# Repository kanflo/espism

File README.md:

# Espism

This repo contins schematics and code to build a low cost ISM radio to wifi gateway.

Look at [hardware/v4](https://github.com/kanflo/espism/tree/master/hardware/v4) for the hardware and [verification](https://github.com/kanflo/espism/tree/master/verification) for the software used to do hardware verification. The directory [mqtt_sniffer](https://github.com/kanflo/espism/tree/master/mqtt_sniffer) contains an ISM to MQTT sniffer. Blog post [is here](http://johan.kanflo.com/bridging-ism-radio-and-wifi-for-lunch-money/).

#### Building

```
git clone https://github.com/kanflo/espism.git
cd espism
git submodule init && git submodule update
cd mqtt_sniffer
vi esp-open-rtos/include/private_ssid_config.h # Fix wifi credentials
make && make flash
```

Wifi credentials, in case you did not know, are written to `esp-open-rtos/include/private_ssid_config.h` as 

```
#define WIFI_SSID "your ssid"
#define WIFI_PASS "your key"
```

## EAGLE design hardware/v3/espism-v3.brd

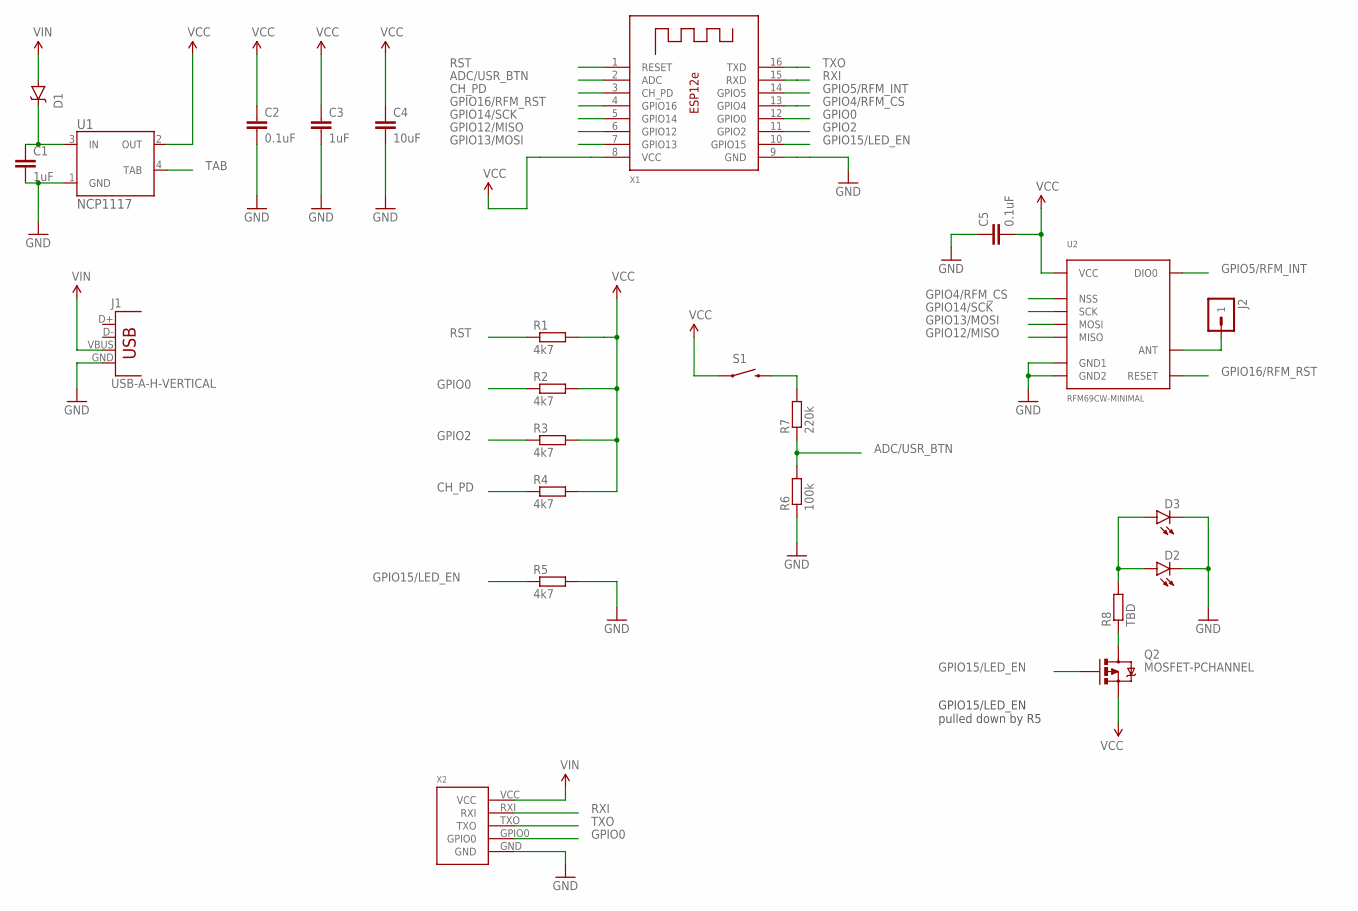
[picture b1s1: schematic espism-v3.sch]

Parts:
C1, C3: 1uF; 0603-CAP
C2, C5: 0.1uF; 0603-CAP
C4: 10uF; 0603-CAP
D1: DIODE-SCHOTTKYSOD-123FL; SOD-123FL
D2, D3: LED0603; LED-0603
J1: USB-A-H-VERTICAL
J2: M01-ANTENNA; 1X01-ANTENNA
Q2: MOSFET-PCHANNEL; SOT23-3
R1, R2, R3, R4, R5: 4k7; R0603
R6: 100k; R0603
R7: 220k; R0603
R8: TBD; R0603
S1: SWITCH-MOMENTARY-2SMD-1101NE; TACTILE-SWITCH-1101NE
U1: NCP1117; SOT223
U2: RFM69CW-MINIMAL
X1: ESP-12E
X2: ESPROGESPROG-DEVICE; ESPROG

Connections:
ADC/USR_BTN: R6.2, R7.1, X1.2 (ADC)
CAM_VCC: Q2.3 (D), R8.1
CH_PD: R4.1, X1.3 (CH_PD)
GND: C1.2, C2.2, C3.2, C4.2, C5.1, D2.C, D3.C, J1.GND, R5.2, R6.1, U1.1 (GND), U2.GND@1 (GND1), U2.GND@2 (GND2), X1.9 (GND), X2.GND
GPIO0: R2.1, X1.12 (GPIO0), X2.GPIO0
GPIO2: R3.1, X1.11 (GPIO2)
GPIO4/RFM_CS: U2.NSS, X1.13 (GPIO4)
GPIO5/RFM_INT: U2.DIO0, X1.14 (GPIO5)
GPIO12/MISO: U2.MISO, X1.6 (GPIO12)
GPIO13/MOSI: U2.MOSI, X1.7 (GPIO13)
GPIO14/SCK: U2.SCK, X1.5 (GPIO14)
GPIO15/LED_EN: Q2.1 (G), R5.1, X1.10 (GPIO15)
GPIO16/RFM_RST: U2.RESET, X1.4 (GPIO16)
unnamed: D2.A, D3.A, R8.2
unnamed: C1.1, D1.C, U1.3 (IN)
unnamed: J2.1, U2.ANT
unnamed: R7.2, S1.2
RST: R1.1, X1.1 (RESET)
RXI: X1.15 (RXD), X2.RXI
TAB: U1.4 (TAB)
TXO: X1.16 (TXD), X2.TXO
VCC: C2.1, C3.1, C4.1, C5.2, Q2.2 (S), R1.2, R2.2, R3.2, R4.2, S1.1, U1.2 (OUT), U2.VDD (VCC), X1.8 (VCC)
VIN: D1.A, J1.VBUS, X2.VCC

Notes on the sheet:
GPIO15/LED_EN pulled down by R5

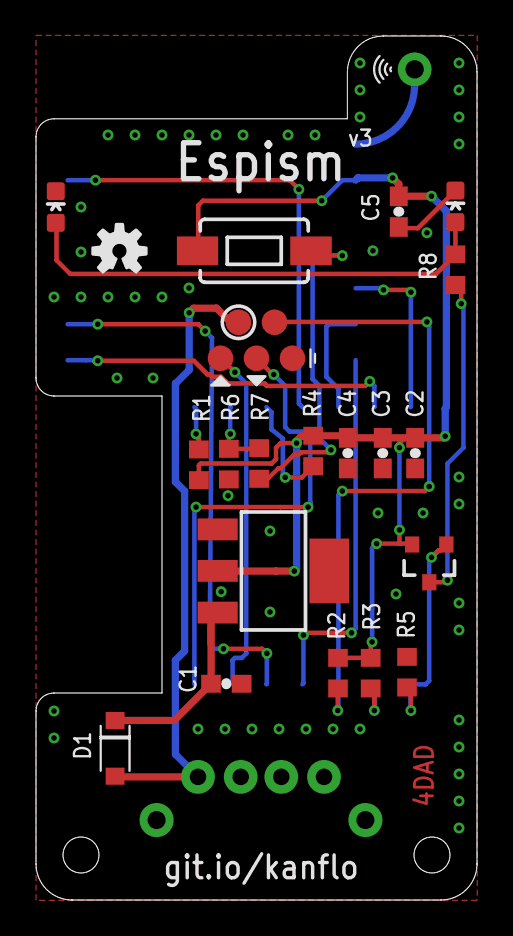
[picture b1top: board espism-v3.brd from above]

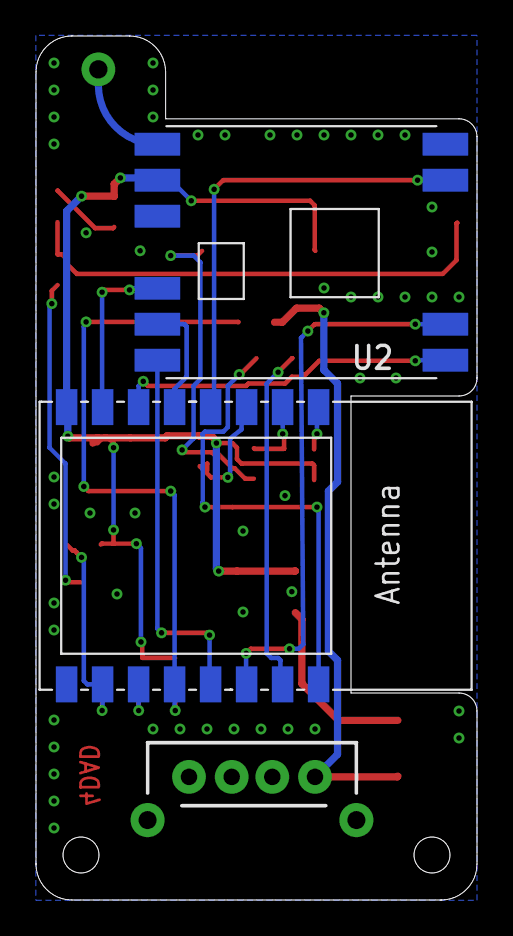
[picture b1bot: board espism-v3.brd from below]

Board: 2 copper layers, 24.5 x 48.0 mm, 25 parts (3 on the bottom side), 22 nets.

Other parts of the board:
U$2: OSHW-LOGO-S

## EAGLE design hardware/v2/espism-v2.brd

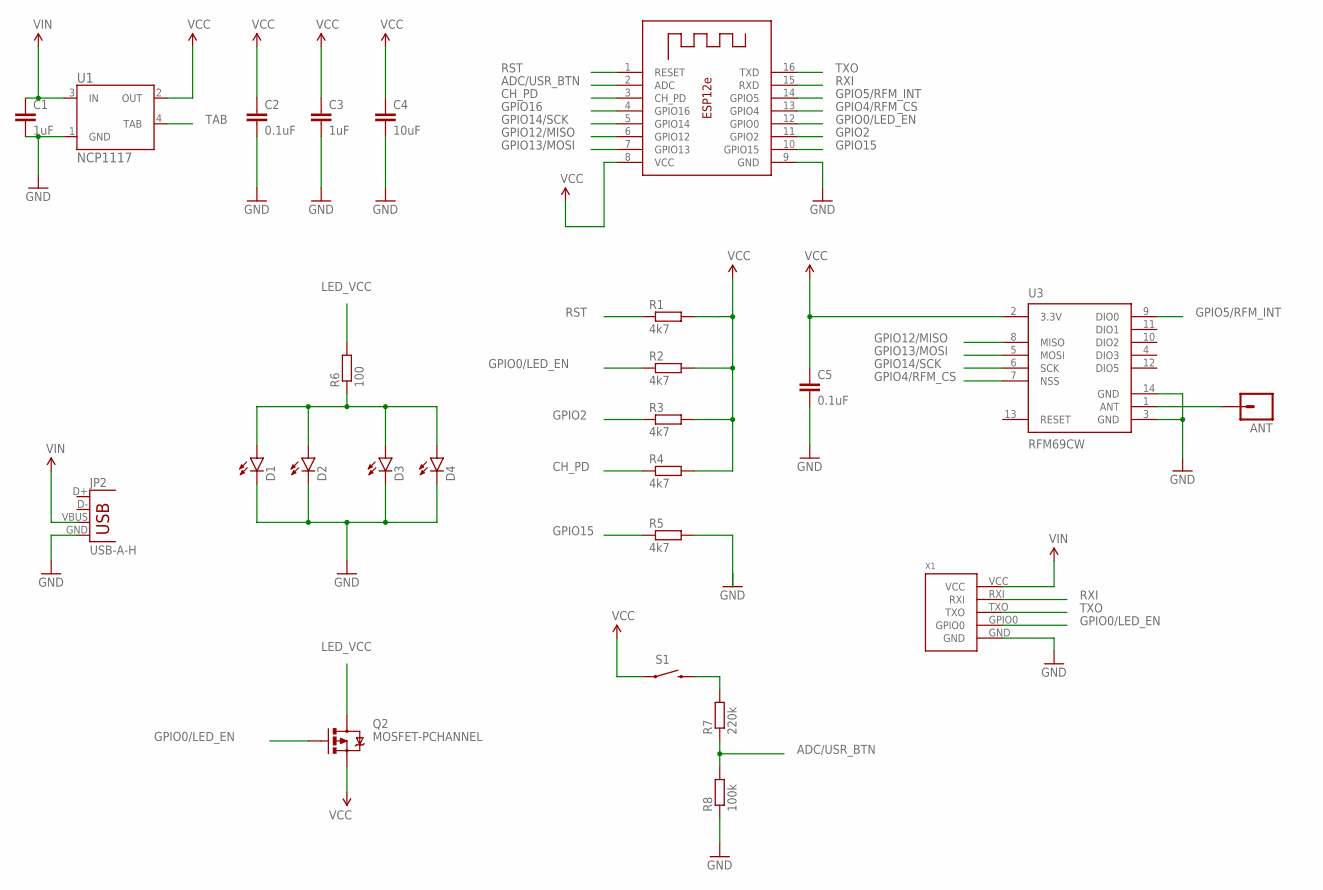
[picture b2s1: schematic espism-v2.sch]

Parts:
ANT: M01PTH; 1X01
C1, C3: 1uF; 0603-CAP
C2, C5: 0.1uF; 0603-CAP
C4: 10uF; 0603-CAP
D1, D2, D3, D4: LED0603; LED-0603
JP2: USB-A-H
Q2: MOSFET-PCHANNEL; SOT23-3
R1, R2, R3, R4, R5: 4k7; R0603
R6: 100; R0603
R7: 220k; R0603
R8: 100k; R0603
S1: SWITCH-MOMENTARY-2SMD-1101NE; TACTILE-SWITCH-1101NE
U1: NCP1117; SOT223
U2: ESP-12E
U3: RFM69CW; RFM69CW-XXXS2
X1: ESPROGESPROG-DEVICE; ESPROG

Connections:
ADC/USR_BTN: R7.1, R8.2, U2.2 (ADC)
CH_PD: R4.1, U2.3 (CH_PD)
GND: C1.2, C2.2, C3.2, C4.2, C5.2, D1.C, D2.C, D3.C, D4.C, JP2.GND, R5.2, R8.1, U1.1 (GND), U2.9 (GND), U3.3 (GND), U3.14 (GND), X1.GND
GPIO0/LED_EN: Q2.1 (G), R2.1, U2.12 (GPIO0), X1.GPIO0
GPIO2: R3.1, U2.11 (GPIO2)
GPIO4/RFM_CS: U2.13 (GPIO4), U3.7 (NSS)
GPIO5/RFM_INT: U2.14 (GPIO5), U3.9 (DIO0)
GPIO12/MISO: U2.6 (GPIO12), U3.8 (MISO)
GPIO13/MOSI: U2.7 (GPIO13), U3.5 (MOSI)
GPIO14/SCK: U2.5 (GPIO14), U3.6 (SCK)
GPIO15: R5.1, U2.10 (GPIO15)
GPIO16: U2.4 (GPIO16)
LED_VCC: Q2.3 (D), R6.2
unnamed: ANT.1, U3.1 (ANT)
unnamed: D1.A, D2.A, D3.A, D4.A, R6.1
unnamed: R7.2, S1.2
RST: R1.1, U2.1 (RESET)
RXI: U2.15 (RXD), X1.RXI
TAB: U1.4 (TAB)
TXO: U2.16 (TXD), X1.TXO
VCC: C2.1, C3.1, C4.1, C5.1, Q2.2 (S), R1.2, R2.2, R3.2, R4.2, S1.1, U1.2 (OUT), U2.8 (VCC), U3.2 (3.3V)
VIN: C1.1, JP2.VBUS, U1.3 (IN), X1.VCC

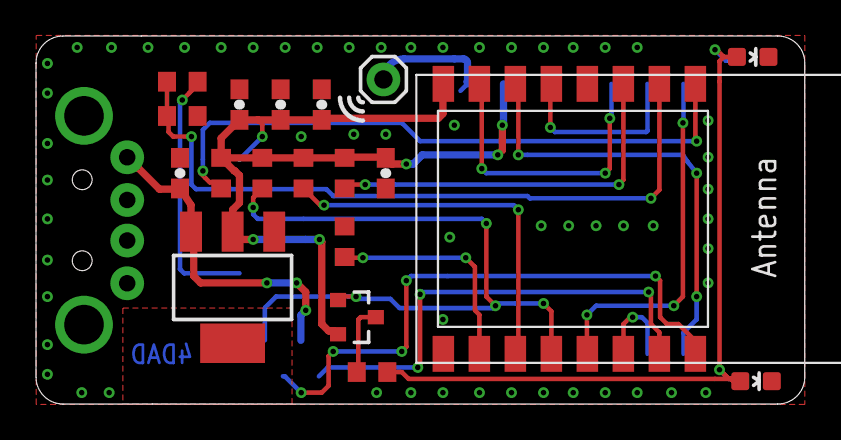
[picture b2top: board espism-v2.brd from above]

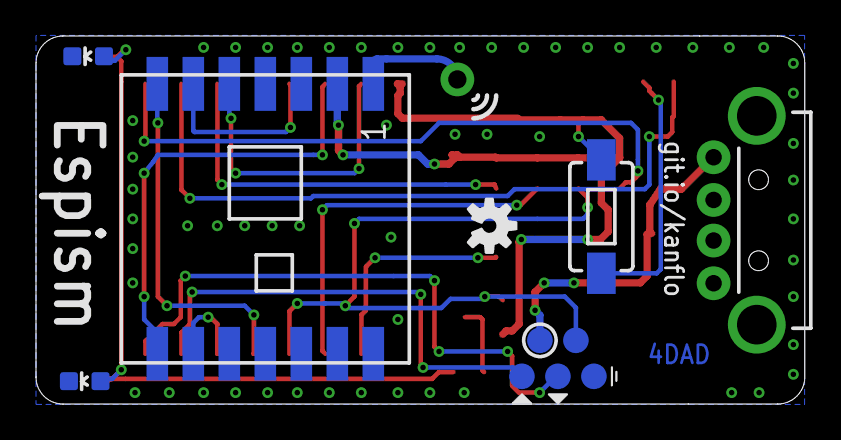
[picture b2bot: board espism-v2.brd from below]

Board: 2 copper layers, 42.7 x 20.4 mm, 26 parts (7 on the bottom side), 20 nets.

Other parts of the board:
U$1: OSHW-LOGO-S

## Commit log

2016-10-12 Updated after MQTT rename Changed MQTT broker to iot.eclipse.org
2016-10-12 Increased publish queue depth
2016-11-13 Corrected HW revision in schematics
2016-11-13 Added support for Espism v3 Updated FreeRTOS API #1
2020-01-10 Updated to latest EOR EOR now a submodule RFM69 driver now a submodule Removed legacy SPI driver
2020-01-10 HW rev 3 and 4
2020-01-10 Updated readme for new HW

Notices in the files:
parts and their libraries:
SparkFun-DiscreteSemi: Licensing: Creative Commons ShareAlike 4.0 International - https://creativecommons.org/licenses/by-sa/4.0
